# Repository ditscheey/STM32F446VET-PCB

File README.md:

# STM32F446VET-PCB
simple breakout board in kicad using jst connectors for i2c, spi uart1, uart2.

additionally adding a DCMI connector for a simple VGA camera (https://www.arducam.com/product/arducam-ov7670-0-3-megapixel-camera-module-for-arduino-boards/)

programming interface for ST-Link

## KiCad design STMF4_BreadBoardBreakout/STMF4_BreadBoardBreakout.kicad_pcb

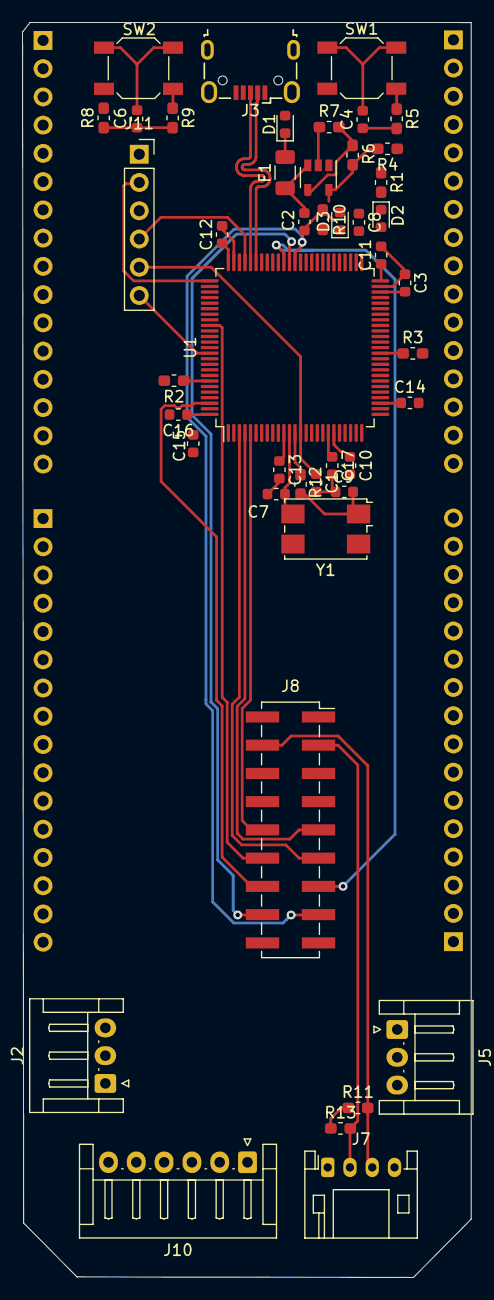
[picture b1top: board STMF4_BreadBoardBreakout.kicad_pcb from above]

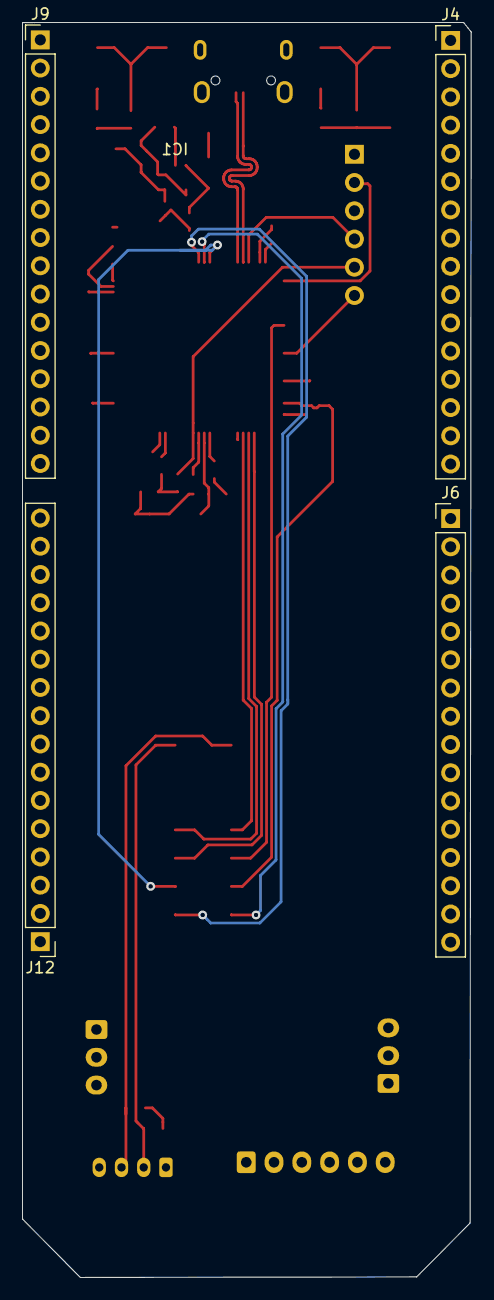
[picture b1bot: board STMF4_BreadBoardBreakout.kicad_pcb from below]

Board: 2 copper layers, 40.3 x 112.9 mm, 49 parts (4 on the bottom side), 83 nets.

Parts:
C1, C10, C11, C12, C13, C14, C15, C16: 100nF; C_0603_1608Metric
C2, C8: 1u; C_0603_1608Metric
C3: 2.2uF; C_0603_1608Metric
C4, C6, C7, C9: 10uF; C_0603_1608Metric
C17: 10u; C_0603_1608Metric
D1: todo; D_0603_1608Metric
D2, D3: LED_Status; D_0603_1608Metric
F1: 500mA (max); Fuse_1206_3216Metric
IC1: SGM2019-ADJYN5G-TR; SOT-23-5
J2: USART1; JST_EH_S3B-EH_1x03_P2.50mm_Horizontal
J3: USB_B_Micro; USB_Micro-B_Wuerth_629105150521
J4: PORT B; PinHeader_1x16_P2.54mm_Vertical
J5: USART2; JST_EH_S3B-EH_1x03_P2.50mm_Horizontal
J6: PORT C; PinHeader_1x16_P2.54mm_Vertical
J7: I2C3; JST_PH_S4B-PH-K_1x04_P2.00mm_Horizontal
J8: DCMI SPI CAM; PinSocket_2x09_P2.54mm_Vertical_SMD
J9: PORT D; PinHeader_1x16_P2.54mm_Vertical
J10: SPI1; JST_EH_S6B-EH_1x06_P2.50mm_Horizontal
J11: SWD; PinSocket_1x06_P2.54mm_Vertical
J12: PORT E; PinHeader_1x16_P2.54mm_Vertical
R1, R10, R11, R13: 2.2k; R_0603_1608Metric_Pad1.05x0.95mm_HandSolder
R2, R3, R4, R8, R12: 10k; R_0603_1608Metric_Pad1.05x0.95mm_HandSolder
R5, R9: 1k; R_0603_1608Metric_Pad1.05x0.95mm_HandSolder
R6: 73.2k; R_0603_1608Metric_Pad1.05x0.95mm_HandSolder
R7: 42.2k; R_0603_1608Metric_Pad1.05x0.95mm_HandSolder
SW1: BTN_NRST; SW_SPST_SKQG_WithStem
SW2: BTN_UTIL1; SW_SPST_SKQG_WithStem
U1: STM32F446VETx; LQFP-100_14x14mm_P0.5mm
Y1: Crystal; Crystal_SMD_7050-4Pin_7.0x5.0mm

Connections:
+3.3V: C8.1, C10.1, C11.1, C12.1, C13.1, C14.1, C15.1, C16.1, C17.1, D3.2, IC1.5, R4.2, R6.1, R8.2, R11.1, R13.1, U1.6, U1.11, U1.19, U1.22, U1.28, U1.50, U1.75, U1.100
+3V3: J7.1, J8.1, J10.1, J11.1
+5V: D1.2, J3.1
BOOT0: R2.1, U1.94
BOOT1: J4.3, R3.1, U1.37
DCMI_D0: J6.7, J8.15, U1.63
DCMI_D1: J6.8, J8.16, U1.64
DCMI_D2: J6.9, J8.13, U1.65
DCMI_D3: J8.14, J12.2, U1.98
DCMI_D4: J8.11, J12.5, U1.3
DCMI_D5: J8.12, J9.3, U1.84
DCMI_D6: J8.9, J12.6, U1.4
DCMI_D7: J8.10, J12.7, U1.5
GND: C1.2, C2.2, C3.2, C4.2, C6.2, C7.2, C8.2, C9.2, C10.2, C11.2, C12.2, C13.2, C14.2, C15.2, C16.2, C17.2, IC1.2, J2.3, J3.5, J5.3, J7.4, J8.2, J8.5, J8.6, J8.7, J8.17, J8.18, J10.6, J11.3, R1.1, R2.2, R3.2, R7.2, R10.2, SW1.2, SW2.2, U1.10, U1.20, U1.27, U1.49, U1.74, U1.99
HSE_IN: C7.1, U1.12, Y1.2
HSE_OUT: R12.1, U1.13
I2C3_SCL: J7.3, J8.4, R11.2
I2C3_SDA: J6.10, J7.2, J8.3, R13.2
LED_STATUS: D2.2, U1.54
NRST: C1.1, J11.5, U1.14
unnamed: C2.1, F1.1, IC1.1, IC1.3
unnamed: C4.1, R4.1, R5.2
unnamed: C6.1, R8.1, R9.2
unnamed: C9.1, R12.2, Y1.1
unnamed: D1.1, F1.2
unnamed: D2.1, R1.2
unnamed: D3.1, R10.1
unnamed: IC1.4, R6.2, R7.1
unnamed: R5.1, SW1.1
unnamed: R9.1, SW2.1
PB0: J4.1, U1.35
PB1: J4.2, U1.36
PB4: J4.5, U1.90
PB5: J4.6, U1.91
PB7: J4.8, U1.93
PB8: J4.9, U1.95
PB9: J4.10, U1.96
PB10: J4.11, U1.47
PB12: J4.12, U1.51
PB13: J4.13, U1.52
PB14: J4.14, U1.53
PC0: J6.1, U1.15
PC1: J6.2, U1.16
PC2: J6.3, U1.17
PC3: J6.4, U1.18
PC4: J6.5, U1.33
PC5: J6.6, U1.34
PC10: J6.11, U1.78
PC11: J6.12, U1.79
PC12: J6.13, U1.80
PC13: J6.14, U1.7
PC14: J6.15, U1.8
PC15: J6.16, U1.9
PD4: J9.5, U1.85
PD5: J9.6, U1.86
PD6: J9.7, U1.87
PD7: J9.8, U1.88
PD8: J9.9, U1.55
PD9: J9.10, U1.56
PD10: J9.11, U1.57
PD11: J9.12, U1.58
PD12: J9.13, U1.59
PD13: J9.14, U1.60
PD14: J9.15, U1.61
PD15: J9.16, U1.62
PE0: J12.1, U1.97
PE2: J12.3, U1.1
PE3: J12.4, U1.2
PE7: J12.8, U1.38
PE8: J12.9, U1.39
PE9: J12.10, U1.40
PE10: J12.11, U1.41
PE11: J12.12, U1.42
PE12: J12.13, U1.43
PE13: J12.14, U1.44
PE14: J12.15, U1.45
PE15: J12.16, U1.46
SYS_SWCLK: J11.2, U1.76
SYS_SWDIO: J11.4, U1.72
SYS_SWO: J11.6, U1.89
USB_FS_+: J3.3, U1.71
USB_FS_-: J3.2, U1.70
vCAP_1: C3.1, U1.48

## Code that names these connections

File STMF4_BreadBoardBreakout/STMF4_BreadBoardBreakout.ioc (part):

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Mcu.Name=STM32F446V(C-E)Tx
Mcu.Package=LQFP100
Mcu.UserName=STM32F446VETx
PA10.Mode=Asynchronous
PA10.Signal=USART1_RX
PA11.Mode=Host_Only
PA11.Signal=USB_OTG_FS_DM
PA12.Mode=Host_Only
PA12.Signal=USB_OTG_FS_DP
PA13.Mode=Trace_Asynchronous_SW
PA13.Signal=SYS_JTMS-SWDIO
PA14.Mode=Trace_Asynchronous_SW
PA14.Signal=SYS_JTCK-SWCLK
PA2.Mode=Asynchronous
PA2.Signal=USART2_TX
PA3.Mode=Asynchronous
PA3.Signal=USART2_RX
PA5.Mode=Full_Duplex_Master
PA5.Signal=SPI1_SCK
PA6.Mode=Slave_8_bits_Embedded_Synchro
PA6.Signal=DCMI_PIXCLK
PA7.Mode=Full_Duplex_Master
PA7.Signal=SPI1_MOSI
PA8.Mode=I2C
PA8.Signal=I2C3_SCL
PB3.Mode=Trace_Asynchronous_SW
PB3.Signal=SYS_JTDO-SWO
PB4.Mode=Full_Duplex_Master
PB4.Signal=SPI1_MISO
PB6.Mode=Asynchronous
PB6.Signal=USART1_TX
PC6.Mode=Slave_8_bits_Embedded_Synchro
PC6.Signal=DCMI_D0
PC7.Mode=Slave_8_bits_Embedded_Synchro
PC7.Signal=DCMI_D1
PC8.Mode=Slave_8_bits_Embedded_Synchro
PC8.Signal=DCMI_D2
PC9.Mode=I2C
PC9.Signal=I2C3_SDA
PD0.Mode=Master
PD0.Signal=CAN1_RX
PD1.Mode=Master
PD1.Signal=CAN1_TX
PD3.Mode=Slave_8_bits_Embedded_Synchro
PD3.Signal=DCMI_D5
PE1.Mode=Slave_8_bits_Embedded_Synchro
PE1.Signal=DCMI_D3
PE4.Mode=Slave_8_bits_Embedded_Synchro
PE4.Signal=DCMI_D4
PE5.Mode=Slave_8_bits_Embedded_Synchro
PE5.Signal=DCMI_D6
PE6.Mode=Slave_8_bits_Embedded_Synchro
PE6.Signal=DCMI_D7
PH0-OSC_IN.Mode=HSE-External-Oscillator
PH0-OSC_IN.Signal=RCC_OSC_IN
PH1-OSC_OUT.Mode=HSE-External-Oscillator
PH1-OSC_OUT.Signal=RCC_OSC_OUT
RCC.HSE_VALUE=20000000
RCC.SYSCLKFreq_VALUE=52000000
RCC.SYSCLKSource=RCC_SYSCLKSOURCE_PLLCLK
board=custom

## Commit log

2020-08-29 rough sketch finished
2020-08-31 rough component placement, change to smd
2020-08-31 move connectors and mcu in sub schematic
2020-09-01 reduce size in pcb, fix second sheet, main routing finished
